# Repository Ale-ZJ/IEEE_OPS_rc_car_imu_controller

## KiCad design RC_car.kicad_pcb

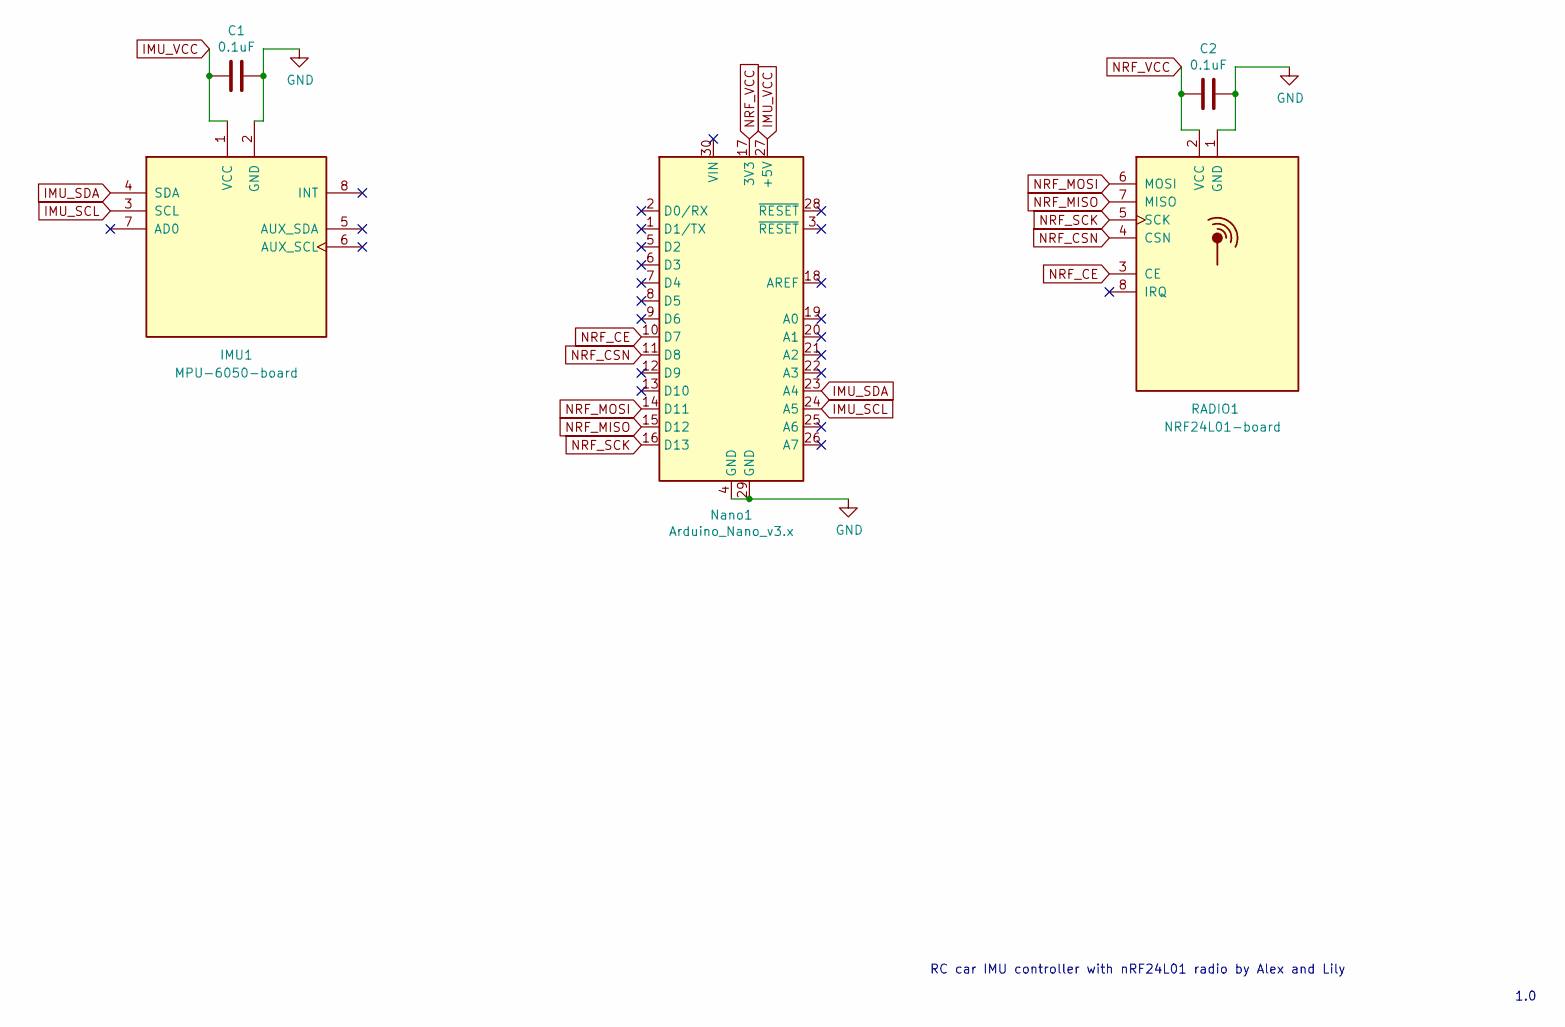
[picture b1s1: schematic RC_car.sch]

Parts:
C1, C2: 0.1uF; C_0805_2012Metric_Pad1.18x1.45mm_HandSolder
IMU1: MPU-6050-board; IMU_board
Nano1: Arduino_Nano_v3.x; Arduino_Nano
RADIO1: NRF24L01-board; Radio_board

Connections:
GND: C1.1, C2.1, IMU1.2 (GND), Nano1.4 (GND), Nano1.29 (GND), RADIO1.1 (GND)
IMU_SCL: IMU1.3 (SCL), Nano1.24 (A5)
IMU_SDA: IMU1.4 (SDA), Nano1.23 (A4)
IMU_VCC: C1.2, IMU1.1 (VCC), Nano1.27 (+5V)
NRF_CE: Nano1.10 (D7), RADIO1.3 (CE)
NRF_CSN: Nano1.11 (D8), RADIO1.4 (CSN)
NRF_MISO: Nano1.15 (D12), RADIO1.7 (MISO)
NRF_MOSI: Nano1.14 (D11), RADIO1.6 (MOSI)
NRF_SCK: Nano1.16 (D13), RADIO1.5 (SCK)
NRF_VCC: C2.2, Nano1.17 (3V3), RADIO1.2 (VCC)

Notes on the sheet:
RC car IMU controller with nRF24L01 radio by Alex and Lily
1.0

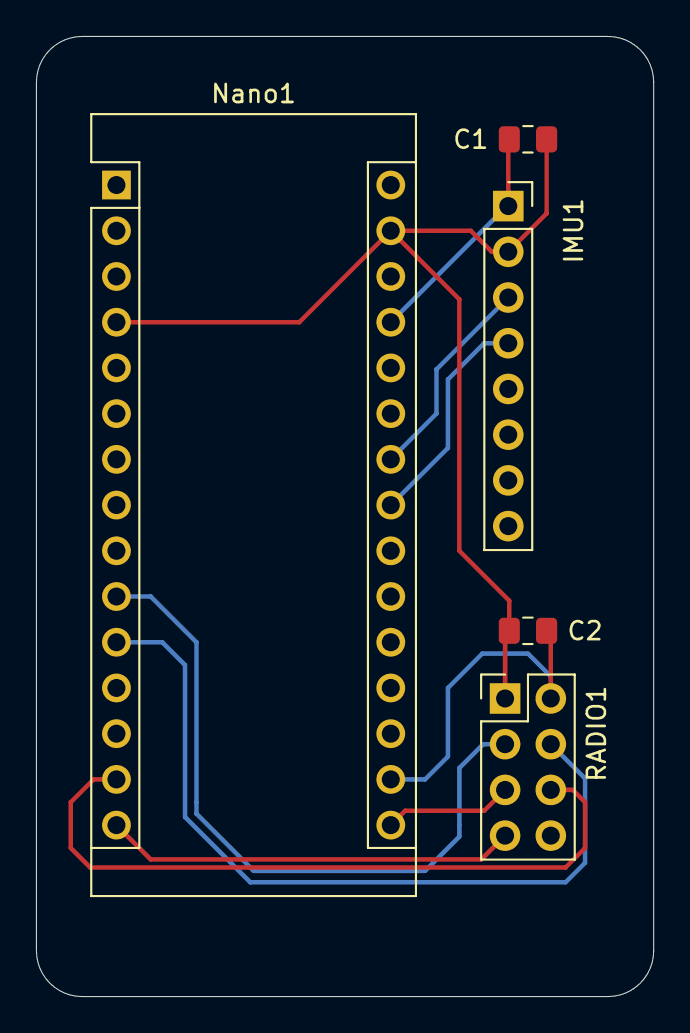
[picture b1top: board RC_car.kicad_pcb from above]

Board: 2 copper layers, 34.3 x 53.3 mm, 5 parts (0 on the bottom side), 10 nets.
